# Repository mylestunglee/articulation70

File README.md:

# articulation70

The _articulation70_ keyboard is a successor to the [articulation80](https://github.com/mylestunglee/articulation80), with LEDs and a more personalised layout.

It features:
- Variable pinky stagger, supporting ±1 mm vertically offsetted soldering configurations.
- 3 × 6 main body, 3 thumb switches, 2 corner switches and 3 × 4 numpad layout.
- Kailh Choc V1 hot-swap support.
- A breakaway-able number pad.
- Serial or I2C connection between halves.
- Pro Micro-compatible controller support, however a micro-controller. with more pins are required to operate LEDs 2 and 3.
- 3 LEDs
- Reversible PCB to reduce manufacturing costs for hobby usage.

## KiCad plugins

This repo comes included with two plugins. To install these plugins, copy the directories in `plugins` into your _Plugins Directory_, which is found by _Tools → External Plugins → Open Plugins Directory_ in the PCB Editor.

### Split intersecting traces

When joining traces from rotated switches, it can be difficult to connect traces from two angles to form a aesthetic curve. This plugins splits two selected intersecting traces into four traces.

An example of use:

### Total trace length

Why not?

## Build Instructions

This build is very similar to many hobby keyboards. Please refer to the instructions for  [articulation80](https://github.com/mylestunglee/articulation80). You will need a soldering iron.

#### Which jumpers do I need to solder?

If using serial, then solder J1, and J4. If using I2C, then solder J2, J3 and J4. Solder on the back of each respective half.

### Build Parts

I would recommend substituting for cheaper or easier to source components when possible.

| Component | Quantity | MPN | Purchase Link | Remarks |
|:-|:-|:-|:-|:-|
| PCB | 2 |
| Left switch plate | 1
| Right switch plate | 1
| Micro-controller plate | 2
| Micro-controller | 2 | Elite-C | [Link](https://mechboards.co.uk/products/elite-c-v4)
| Through-hole TRRS jack | 2 | PJ-320A | [Link](https://mechboards.co.uk/products/trrs-jacks?variant=40330077241549)
| TRRS cable | 1 | | [Link](https://mou.sr/3QC5ykN) | Also called a 4-pin 3.5mm audio auxiliary cable |
| Reset button | 2 | PTS526 SM15 SMTR2 LFS | [Link](https://mou.sr/3tXtsOQ) | Different button operating force are possible
| LED | 3 | HLMP-1401 | [Link](https://mou.sr/45Zy9Vw) | Any T1 size
| 150Ω Resistor  | 3 | RC1206FR-07150RL | [Link](https://mou.sr/3QEyQzo) | Optional, for LEDs
| 4.7kΩ Resistor  | 2 | RC1206FR-104K7L | [Link](https://mou.sr/46XoOPE) | Optional, for I2C connection
| SMD Diode | 70*    | 1N4148W-TP | [Link](https://mou.sr/3D01KSP) | Any SOD-123 size |
| Hot swap micro-controller sockets | 5 | 315-43-112-41-003000 | [Link](https://mou.sr/3QfEIO2) | Recommended
| Hot swap pins | 52 | 3320-0-00-15-00-00-03-0 | [Link](https://mou.sr/3tYd80f) | Recommended |
| Rubber feet | 12** | SJ-5302 CLEAR | [Link](https://mou.sr/3QFq1oL)
| Hot swap key sockets | 70*      | CPG135001S30 | [Link](https://mechboards.co.uk/products/kailh-choc-hotswap-sockets)
| Key Switch | 70* | CPG135001 | [Link](https://www.aliexpress.com/item/1005005446722280.html)
| Key Cap | 70* | | | Ideally different key caps for thumbs |
| Stickers | 1 | | [Link](https://www.aliexpress.com/item/1005005222836654.html) | Optional

*Adjust for number of keys desired.

**Adjust for number of numpads.

## How to order PCBs and plates

I ordered from JLCPCB, however there are many other manufacturers. Take a look at [PCBShopper](https://pcbshopper.com/).

For the PCBs, I used:
- Base material: FR-4
- PCB thickness: 1.6 mm
- PCB colour: black
- Surface finish: LeadFree HASL
- Remove order number: Yes

For the switch plates, I used:
- Base material: FR-4
- PCB thickness: 1.2 mm
- PCB colour: black
- Surface finish: HASL (with lead) because the unleaded option greatly increases cost and the plates do not have any pads.
- Remove order number: Yes

For the controller plates, I used:
- Base material: FR-4
- PCB thickness: 1.2 mm
- PCB colour: black
- Surface finish: HASL (with lead)
- Remove order number: Yes

## How to adjust the layout

This was tested on installation of FreeCad 0.20.2, Python 3.11.6 and KiCad 7.0.6.

1. First, open `layout.FCStd` with FreeCad and open _Constants_ under the model tree view. You should see a spreadsheet of parameters.

2. Change values as necessary. If the values change too much from their intended range, then the sketch (as shown in the next step) may become broken.
3. Click on one of the sketches in the model tree view. Verify the layout shown is correct.

4. Export the layout to a file by coping the contents of `scripts/export_geometry.py` into FreeCad's Python console. The console is accessible by _View → Panel → Python console_. If you get a permission error, change `geometry.txt` to an absolute path within the repo. You should get a number, which reports the bytes written to `geometry.txt`.

5. Update the PCB by running the following scripts:

```
python scripts/update_geometry.py pcb/keyboard.kicad_pcb geometry.txt
python scripts/update_geometry.py left_plate/plate.kicad_pcb geometry.txt
python scripts/update_geometry.py right_plate/plate.kicad_pcb geometry.txt
```

For now, I will run the first script. Update the PCB files for the plates if desired.

6. Clean-up residual graphic objects on the `Edge.Cuts` layer. The script deletes all previous edges and plots edges in the `Edge` and `EdgeNumpad` sketch, which includes construction lines that should not be included in the `Edge.Cuts` layer. The script also positions footprints according to the `Components` sketch. The script will output some text because some components' positions are not specified by the layout, such as the resistors.

7. Update traces and refill copper zones. Unfortunately this step takes the longest. Make sure to thoroughly check PCB.

The PCB is ready!

## Firmware

I used [QMK](https://qmk.fm/) program the controllers. To use the same setup as me, copy the contents of `qmk` directory into your installation of `qmk_firmware/keyboards`. Flash the left and right controllers with the respective commands:
```
qmk flash -kb articulation70 -km default -bl dfu-split-left
qmk flash -kb articulation70 -km default -bl dfu-split-right
```
These commands assume the usage of Elite-C's.

If you want to upgrade the toolchain, you can do so at your own risk:
```
pacboy update avr-gcc:x
```

## Additional documentation

```
scripts/corner_switch_pad_geometry.py
scripts/curved_switch_pad_geometry.py
```

These switches generate the geometry for curved pads featured in the switch footprints. The curved shape comes from the rectangular pad subtracted by the clearance of the centre switch drill hole. KiCad supports polygons in pads, but it is not very easy to use. These scripts makes the design of these footprints a bit easier.

## Gallery

More images can be found [here](https://github.com/mylestunglee/articulation70/tree/master/images).

## Future Considerations

There are a few improvements that can be made:

- Adding a pattern to improve aesthetics on the plates.
- Adding solder mask expansion on pads and pins.
- Re-route `ROW4` trace.
- Support LED placement in top-right.
- Improve LED brightness as they are too dim.
- Support both micro-controllers mounted face down.
- Strive to continually improve layout. The key columns are perpendicular to the fingers. This does not effectively utilise the flexibility of the hand.

## Credit

Thanks to:
- [KBD.news](https://kbd.news/) for inspiration.
- `sevmyer` for the [open-source KiCad teardrop plugin](https://github.com/sevmeyer/kicad-arc-teardrops) which was very helpful given many KiCad teardrop plugins were for Kicad 6.
- The QMK community on Discord for their helpful explanations.
- Various open source keyboards for guidance, but not limited to: [KLOTZ](https://github.com/GEIGEIGEIST/KLOTZ), [Corne](https://github.com/foostan/crkbd) and [Breeze](https://www.afternoonlabs.com/breeze/).

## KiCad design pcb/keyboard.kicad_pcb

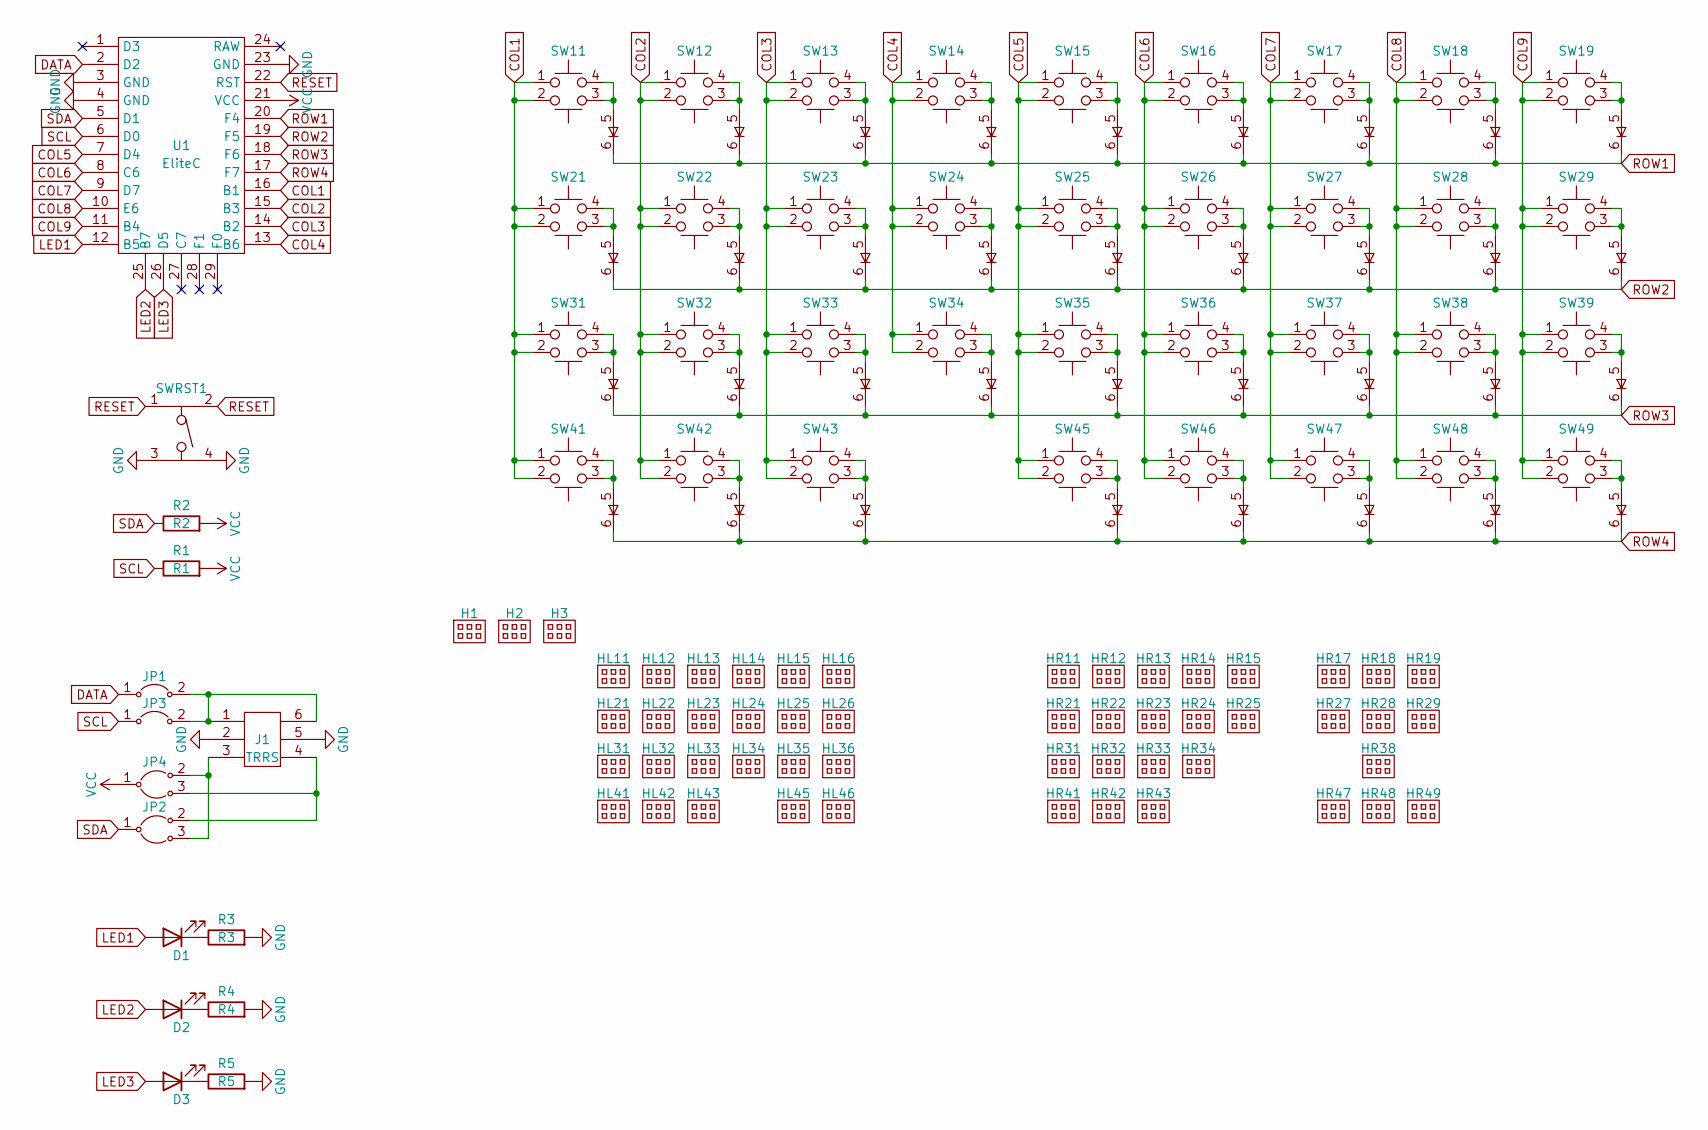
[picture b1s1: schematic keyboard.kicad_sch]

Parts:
D1: LED1; HLMP-1401
D2: LED2; HLMP-1401
D3: LED3; HLMP-1401
H1: H1; RightPlate
H2: H2; LeftPlate
H3: H2; ControllerPlate
HL11, HL12, HL13, HL14, HL15, HL21, HL22, HL23, HL24, HL25, HL31, HL32, HL33, HL34, HL41, HL42, HL43: Switch3DLeft
HL16, HL26, HL35, HL36, HL45, HL46: SwitchDoubleLeft
HR11, HR12, HR13, HR14, HR15, HR17, HR18, HR19, HR21, HR22, HR23, HR24, HR25, HR27, HR28, HR29, HR31, HR32, HR33, HR34, HR38, HR41, HR42, HR43, HR47, HR48, HR49: Switch3DRight
J1: TRRS; PJ-320A
JP1: J1; Jumper
JP2: J2; JumperSplit
JP3: J3; Jumper
JP4: J4; JumperSplit
R1: R1; SDR18
R2: R2; SDR18
R3: R3; SDR18
R4: R4; SDR18
R5: R5; SDR18
SW11: 11; Switch
SW12: 12; Switch
SW13: 13; Switch
SW14: 14; Switch
SW15: 15; Switch
SW16: 16; SwitchDoubleRight
SW17: 17; Switch
SW18: 18; Switch
SW19: 19; Switch
SW21: 21; Switch
SW22: 22; Switch
SW23: 23; Switch
SW24: 24; Switch
SW25: 25; Switch
SW26: 26; SwitchDoubleRight
SW27: 27; Switch
SW28: 28; Switch
SW29: 29; Switch
SW31: 31; Switch
SW32: 32; Switch
SW33: 33; Switch
SW34: 34; Switch
SW35: 35; SwitchDoubleRight
SW36: 36; SwitchDoubleRight
SW37: 37; Switch
SW38: 38; Switch
SW39: 39; Switch
SW41: 41; Switch
SW42: 42; Switch
SW43: 43; Switch
SW45: 45; SwitchDoubleRight
SW46: 46; SwitchDoubleRight
SW47: 47; Switch
SW48: 48; Switch
SW49: 49; Switch
SWRST1: PTS526
U1: EliteC

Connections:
COL1: SW11.1, SW11.2, SW21.1, SW21.2, SW31.1, SW31.2, SW41.1, SW41.2, U1.16 (B1)
COL2: SW12.1, SW12.2, SW22.1, SW22.2, SW32.1, SW32.2, SW42.1, SW42.2, U1.15 (B3)
COL3: SW13.1, SW13.2, SW23.1, SW23.2, SW33.1, SW33.2, SW43.1, SW43.2, U1.14 (B2)
COL4: SW14.1, SW14.2, SW24.1, SW24.2, SW34.1, SW34.2, U1.13 (B6)
COL5: SW15.1, SW15.2, SW25.1, SW25.2, SW35.1, SW35.2, SW45.1, SW45.2, U1.7 (D4)
COL6: SW16.1, SW16.2, SW26.1, SW26.2, SW36.1, SW36.2, SW46.1, SW46.2, U1.8 (C6)
COL7: SW17.1, SW17.2, SW27.1, SW27.2, SW37.1, SW37.2, SW47.1, SW47.2, U1.9 (D7)
COL8: SW18.1, SW18.2, SW28.1, SW28.2, SW38.1, SW38.2, SW48.1, SW48.2, U1.10 (E6)
COL9: SW19.1, SW19.2, SW29.1, SW29.2, SW39.1, SW39.2, SW49.1, SW49.2, U1.11 (B4)
DATA: JP1.1, U1.2 (D2)
GND: J1.2, J1.5, R3.2, R4.2, R5.2, SWRST1.3, SWRST1.4, U1.3 (GND), U1.4 (GND), U1.23 (GND)
LED1: D1.2 (A), U1.12 (B5)
LED2: D2.2 (A), U1.25 (B7)
LED3: D3.2 (A), U1.26 (D5)
unnamed: D1.1 (K), R3.1
unnamed: D2.1 (K), R4.1
unnamed: D3.1 (K), R5.1
unnamed: J1.1, J1.6, JP1.2, JP3.2
unnamed: J1.3, JP2.3, JP4.2
unnamed: J1.4, JP2.2, JP4.3
unnamed: SW11.3, SW11.4, SW11.5
unnamed: SW12.3, SW12.4, SW12.5
unnamed: SW13.3, SW13.4, SW13.5
unnamed: SW14.3, SW14.4, SW14.5
unnamed: SW15.3, SW15.4, SW15.5
unnamed: SW16.3, SW16.4, SW16.5
unnamed: SW17.3, SW17.4, SW17.5
unnamed: SW18.3, SW18.4, SW18.5
unnamed: SW19.3, SW19.4, SW19.5
unnamed: SW21.3, SW21.4, SW21.5
unnamed: SW22.3, SW22.4, SW22.5
unnamed: SW23.3, SW23.4, SW23.5
unnamed: SW24.3, SW24.4, SW24.5
unnamed: SW25.3, SW25.4, SW25.5
unnamed: SW26.3, SW26.4, SW26.5
unnamed: SW27.3, SW27.4, SW27.5
unnamed: SW28.3, SW28.4, SW28.5
unnamed: SW29.3, SW29.4, SW29.5
unnamed: SW31.3, SW31.4, SW31.5
unnamed: SW32.3, SW32.4, SW32.5
unnamed: SW33.3, SW33.4, SW33.5
unnamed: SW34.3, SW34.4, SW34.5
unnamed: SW35.3, SW35.4, SW35.5
unnamed: SW36.3, SW36.4, SW36.5
unnamed: SW37.3, SW37.4, SW37.5
unnamed: SW38.3, SW38.4, SW38.5
unnamed: SW39.3, SW39.4, SW39.5
unnamed: SW41.3, SW41.4, SW41.5
unnamed: SW42.3, SW42.4, SW42.5
unnamed: SW43.3, SW43.4, SW43.5
unnamed: SW45.3, SW45.4, SW45.5
unnamed: SW46.3, SW46.4, SW46.5
unnamed: SW47.3, SW47.4, SW47.5
unnamed: SW48.3, SW48.4, SW48.5
unnamed: SW49.3, SW49.4, SW49.5
RESET: SWRST1.1, SWRST1.2, U1.22 (RST)
ROW1: SW11.6, SW12.6, SW13.6, SW14.6, SW15.6, SW16.6, SW17.6, SW18.6, SW19.6, U1.20 (F4)
ROW2: SW21.6, SW22.6, SW23.6, SW24.6, SW25.6, SW26.6, SW27.6, SW28.6, SW29.6, U1.19 (F5)
ROW3: SW31.6, SW32.6, SW33.6, SW34.6, SW35.6, SW36.6, SW37.6, SW38.6, SW39.6, U1.18 (F6)
ROW4: SW41.6, SW42.6, SW43.6, SW45.6, SW46.6, SW47.6, SW48.6, SW49.6, U1.17 (F7)
SCL: JP3.1, R1.1, U1.6 (D0)
SDA: JP2.1, R2.1, U1.5 (D1)
VCC: JP4.1, R1.2, R2.2, U1.21 (VCC)

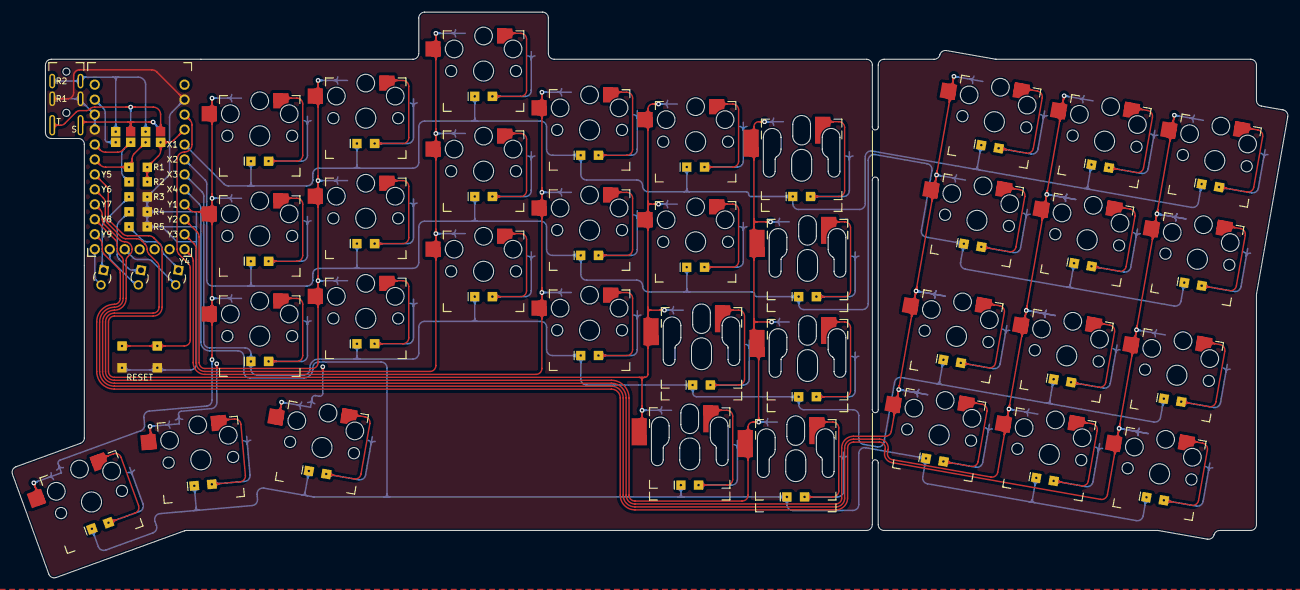
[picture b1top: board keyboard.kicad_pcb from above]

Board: 2 copper layers, 216.6 x 96.0 mm, 103 parts (0 on the bottom side), 63 nets.

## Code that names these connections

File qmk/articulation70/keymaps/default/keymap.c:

#include QMK_KEYBOARD_H
#include "keymap_uk.h"

enum Layers {
    LAYER_BASE,
    LAYER_NUMPAD,
    LAYER_GAME,
    LAYER_LOWER,
    LAYER_UPPER,
    LAYER_ADJUST,
    LAYER_STATUS
};

#define KC_TGNU TG(LAYER_NUMPAD)
#define KC_TGGA TG(LAYER_GAME)
#define KC_MOST MO(LAYER_STATUS)
#define LED1 B5
#define LED2 B7
#define LED3 D5
#define LED_BLINK_DURATION 1000

const uint16_t PROGMEM keymaps[][MATRIX_ROWS][MATRIX_COLS] = {
    [LAYER_BASE] = LAYOUT_split(
        KC_ESC  , KC_F4   , KC_L    , KC_D    , KC_W    , KC_Q              ,           KC_QUOT , KC_F    , KC_O    , KC_U    , KC_PSCR , KC_BSPC , KC_INS  , KC_HOME , KC_PGUP ,
        KC_TAB  , KC_B    , KC_R    , KC_T    , KC_S    , KC_G              ,           KC_Y    , KC_H    , KC_A    , KC_E    , KC_J    , KC_ENT  , KC_DEL  , KC_END  , KC_PGDN ,
        KC_LSFT , KC_N    , KC_X    , KC_M    , KC_C    , KC_V              ,           KC_K    , KC_P    , KC_COMM , KC_DOT  , KC_I    , KC_RSFT           , KC_UP   ,
        KC_LCTL , KC_Z    ,                     KC_LALT , KC_BSPC , TL_LOWR , TL_UPPR , KC_SPC  , KC_RGUI                     , KC_SLSH , KC_RCTL , KC_LEFT , KC_DOWN , KC_RGHT
    ),
    [LAYER_NUMPAD] = LAYOUT_split(
        _______ , _______ , _______ , _______ , _______ , _______           ,           KC_PSLS , KC_P7   , KC_P8   , KC_P9   , KC_PMNS , _______ , _______ , _______ , _______ ,
        _______ , _______ , _______ , _______ , _______ , _______           ,           KC_PAST , KC_P4   , KC_P5   , KC_P6   , KC_PPLS , KC_PENT , _______ , _______ , _______ ,
        _______ , _______ , _______ , _______ , _______ , _______           ,           KC_NO   , KC_P1   , KC_P2   , KC_P3   , KC_P0   , _______           , _______ ,
        _______ , _______ ,                     _______ , _______ , _______ , _______ , _______ , _______                     , KC_PDOT , _______ , _______ , _______ , _______
    ),
    [LAYER_GAME] = LAYOUT_split(
        _______ , _______ , _______ , _______ , _______ , _______           ,           KC_R    , KC_E    , KC_X    , KC_Q    , KC_ESC  , _______ , _______ , _______ , _______ ,
        _______ , _______ , _______ , _______ , _______ , _______           ,           KC_F    , KC_A    , KC_W    , KC_D    , KC_TAB  , _______ , _______ , _______ , _______ ,
        _______ , _______ , _______ , _______ , _______ , _______           ,           KC_V    , KC_C    , KC_S    , KC_Z    , KC_LSFT , KC_LALT           , _______ ,
        _______ , _______ ,                     _______ , _______ , _______ , _______ , _______ , _______                     , KC_LCTL , UK_BSLS , _______ , _______ , _______
    ),
    [LAYER_LOWER] = LAYOUT_split(
        KC_VOLD , KC_VOLU , UK_HASH , KC_QUOT , KC_SCLN , KC_MOST           ,           KC_NUM  , KC_AMPR , KC_ASTR , KC_LPRN , KC_NO   , _______ , _______ , _______ , _______ ,
        _______ , KC_GRV  , KC_LPRN , KC_RPRN , KC_MINS , KC_MOST           ,           KC_CAPS , KC_DLR  , KC_PERC , KC_CIRC , KC_RPRN , _______ , _______ , _______ , _______ ,
        _______ , KC_EQL  , KC_LCBR , KC_RCBR , KC_NO   , KC_MOST           ,           KC_SCRL , KC_EXLM , UK_DQUO , UK_PND  , KC_NO   , _______           , _______ ,
        _______ , UK_BSLS ,                     _______ , _______ , _______ , _______ , _______ , _______                     , KC_NO   , _______ , _______ , _______ , _______
    ),
    [LAYER_UPPER] = LAYOUT_split(
        KC_VOLD , KC_VOLU , UK_TILD , UK_AT   , KC_COLN , KC_MOST           ,           KC_NUM  , KC_7    , KC_8    , KC_9    , KC_MINS , KC_TGNU , _______ , _______ , _______ ,
        _______ , UK_NOT  , KC_LBRC , KC_RBRC , KC_UNDS , KC_MOST           ,           KC_CAPS , KC_4    , KC_5    , KC_6    , KC_PLUS , KC_PENT , _______ , _______ , _______ ,
        _______ , KC_PLUS , KC_LCBR , KC_RCBR , KC_NO   , KC_MOST           ,           KC_SCRL , KC_1    , KC_2    , KC_3    , KC_0    , _______           , _______ ,
        _______ , UK_PIPE ,                     _______ , _______ , _______ , _______ , _______ , _______                     , KC_DOT  , _______ , _______ , _______ , _______
    ),
    [LAYER_ADJUST] = LAYOUT_split(
        KC_TGGA , KC_NO   , KC_NO   , KC_NO   , KC_NO   , KC_MOST           ,           KC_NUM  , KC_F9   , KC_F10  , KC_F11  , KC_F12  , _______ , _______ , _______ , _______ ,
        _______ , KC_NO   , KC_NO   , KC_NO   , KC_NO   , KC_MOST           ,           KC_CAPS , KC_F5   , KC_F6   , KC_F7   , KC_F8   , _______ , _______ , _______ , _______ ,
        _______ , KC_NO   , KC_NO   , KC_NO   , KC_NO   , KC_MOST           ,           KC_SCRL , KC_F1   , KC_F2   , KC_F3   , KC_F4   , _______           , _______ ,
        _______ , KC_NO   ,                     _______ , _______ , _______ , _______ , _______ , _______                     , KC_NO   , _______ , _______ , _______ , _______
    ),
    [LAYER_STATUS] = LAYOUT_split(
        KC_TGGA , _______ , _______ , _______ , _______ , KC_MOST           ,           _______ , _______ , _______ , _______ , _______ , _______ , _______ , _______ , _______ ,
        _______ , _______ , _______ , _______ , _______ , KC_MOST           ,           _______ , _______ , _______ , _______ , _______ , _______ , _______ , _______ , _______ ,
        _______ , _______ , _______ , _______ , _______ , KC_MOST           ,           _______ , _______ , _______ , _______ , _______ , _______           , _______ ,
        _______ , _______ ,                     _______ , _______ , _______ , _______ , _______ , _______                     , _______ , _______ , _______ , _______ , _______
    )
};

bool g_blink_leds;
led_t g_led_state;
layer_state_t g_layer_state;

void update_leds(void) {
    if (g_blink_leds) {
        writePinHigh(LED1);
        writePinHigh(LED2);
        writePinHigh(LED3);
    } else {
        if (IS_LAYER_ON_STATE(layer_state, LAYER_STATUS)) {
            writePin(LED1, g_led_state.num_lock);
            writePin(LED2, g_led_state.caps_lock);
            writePin(LED3, g_led_state.scroll_lock);
        } else {
            writePin(LED1, IS_LAYER_ON_STATE(g_layer_state, LAYER_LOWER) || IS_LAYER_ON_STATE(g_layer_state, LAYER_ADJUST));
            writePin(LED2, IS_LAYER_ON_STATE(g_layer_state, LAYER_NUMPAD) || IS_LAYER_ON_STATE(g_layer_state, LAYER_UPPER) || IS_LAYER_ON_STATE(g_layer_state, LAYER_ADJUST));
            writePin(LED3, IS_LAYER_ON_STATE(g_layer_state, LAYER_GAME));
        }
    }
}

uint32_t after_led_blink(uint32_t trigger_time, void * args) {
    g_blink_leds = false;
    update_leds();
    return 0u;
}

void keyboard_post_init_user(void) {
    g_blink_leds = true;
    update_leds();
    defer_exec(LED_BLINK_DURATION, after_led_blink, NULL);
}

bool led_update_user(led_t led_state) {
    g_led_state = led_state;
    update_leds();
    return true;
}

layer_state_t layer_state_set_user(layer_state_t layer_state) {
    g_layer_state = layer_state;
    update_leds();
    return layer_state;
}

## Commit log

2023-10-01 init
2023-10-02 add thumb cluster
2023-10-03 adjust more
2023-10-03 more adjustment for minimal curl
2023-10-04 parameterise layout
2023-10-05 add some edges
2023-10-05 tight edges
2023-10-05 parameterise thumb positions
2023-10-05 add more edges
2023-10-05 complete edge loop
2023-10-06 remove numpad and add components to grid
2023-10-06 add rotated numpad
2023-10-06 remove LED suggestions
2023-10-07 add component spacing
2023-10-08 remove edges on snap off
2023-10-08 create new pcb project with sample footprint
2023-10-08 add some footprints and adjust silkscreen
2023-10-08 rename footprint library
2023-10-08 update order of switches
2023-10-08 add schematic
2023-10-08 add LED and fix footprints references and positioning
2023-10-08 remove excess switch in schematic
2023-10-10 script porting of edges from FreeCad to KiCad
2023-10-11 script for footprint placement
2023-10-12 curve pad in switch footprint
2023-10-12 set switch number to silkscreen
2023-10-12 move TRRS to overhang and fix diode positioning
2023-10-13 make adjustments from iteration 11 printout and fix numpad switch positions
2023-10-13 adjust numpad x; add solder mask to jumper; add silkscreen line in snap off
2023-10-13 centre snap to switch pads and test traces
2023-10-14 experiment with switch label and diode positioning
2023-10-14 add lots of traces and remove solder mask from jumpers
2023-10-15 fix switch references
2023-10-15 add traces to numpad
2023-10-16 fix right thumb positioning
2023-10-16 use polygon instead of drill offset for switch footprint
2023-10-16 collapse zero length lines in layout
2023-10-16 adjust measurements from v12
2023-10-17 correct traces with new layout
2023-10-17 add traces for thumb cluster
2023-10-17 add remaining bad traces
2023-10-18 improve tracing around microcontroller
2023-10-18 fix issues with footprints
2023-10-18 fix silkscreen around microcontroller
2023-10-18 move col7 trace around controller
2023-10-18 add ground area and fix teardrops
2023-10-19 remove fill at snap-off; fix teardrop; improve fill edge
2023-10-19 add teardrops to T junctions at traces
2023-10-19 add plate to 3D view
2023-10-19 change plate color; remove 3d models from ignored switches
2023-10-20 fix teardrop for reset button
2023-10-21 improve edges in layout
2023-10-21 move graphical copper arcs to traces; use default teardrop size
2023-10-21 fix reference of LED and add project for right plate
2023-10-21 add left plate; update hole footprints; update STEP files
2023-10-21 support 3d view of left plate
2023-10-22 change snap off thickness to 1.6mm for fab house
2023-10-22 hide back of LED by rotation; resistor after LED
2023-10-23 adjust LED footprint to T1 standard
    update plates and traces
2023-10-24 add copper fill to plates and correct plate silkscreen
2023-10-24 plot gerbers and improve ground trace
2023-10-24 correct silkscreen for TRRS jack; add spreadsheet for component ordering
2023-10-25 fix LED footprints; with radius and centreing
2023-10-25 fix schematic of LED pins
2023-10-25 improve traces around microcontroller
2023-10-26 suggest more stuff to order
2023-10-26 start working on pinky separation; update layout and move some footprints
2023-10-27 improve switch double pads
2023-10-27 move pinky up by 1mm
2023-10-27 update plates with asymmetrical pinky stagger
2023-10-27 update toggling 3D model for left and right sides
2023-10-27 fix DRC footprint type mismatch
2023-10-27 fix silkscreen for double switch
2023-10-29 fix teardrops with taps
2023-10-29 fix minimum silkscreen width
2023-10-29 fix LED footprint name and type
2023-10-29 reduce breakoff gap to 1mm
2023-10-30 use edge cuts for overlapping drill holes
    adjust pads to 0.3mm clearance
2023-10-30 rerun rezone
2023-10-30 add 0.001mm to clearance in curved pads and fix breakoff fill exclusion
2023-10-30 remove silkscreen from right plate
2023-10-30 change plates to 1.2mm
2023-10-31 add plugins
2023-10-31 rework footprints with 3d models
2023-10-31 move 3d footprints into position
2023-10-31 change plate colours to charcoal
2023-11-02 start writing readme
2023-11-02 add layout part in readme; add HL and HR in export script; add page details in pcb
2023-11-02 write KiCad readme; fix colour of left plate
2023-11-02 document plugins; fix layout label
2023-11-02 readme: fix screenshot border; fix link
2023-11-14 add qmk files
2023-11-19 add more README
2023-11-19 correct screenshots; add firmware section to README
2023-11-19 reword credit in readme
2023-11-20 update readme with pcb photo
2023-11-25 add post-boot LED blink
2023-12-07 add controller-plate
2023-12-29 Allow right control and shift in numpad mode
2024-01-01 update images
2024-06-15 Update personal keymap
2024-06-15 Use newer QMK keyboard template
2024-07-06 Extend readme
